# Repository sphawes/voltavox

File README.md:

# Voltavox
Voltavox is a PCB-based phonograph "badge"!

Made primarially from PCBs, you can take a tiny PCB record, place it on the platter, place the needle on the record, and a song begins to play! Put a different record on, and as expected, you'll get a different song.

Voltavox is based heavily on the [Adafruit Audio FX Sound Board](https://www.adafruit.com/product/2217). Using [arturo182](https://github.com/arturo182)'s [FlexyPins](https://lectronz.com/products/flexypin-pack-of-100) and some castellated edges on the record PCBs, each record selectively pulls a different control pin on the Audio FX board to ground, choosing a different track. Dropping the needle onto the record completes the circuit and starts playing the audio. 
The horn is also comprised of PCBs soldered edge-to-edge, with a small speaker inside.

## BOM
### Off The Shelf
| Item | Quantity |
| ---- | -------- |
| [Adafruit Audio FX Sound Board + 2x2W Amp - 16MB](https://www.adafruit.com/product/2217) | 1 |
| [8 Ohm Speaker](https://www.adafruit.com/product/1890) | 1 |
| [1200mAh LiPo Battery](https://www.adafruit.com/product/258) | 1 |
| [Micro-Lipo Charger](https://www.adafruit.com/product/1904) | 1 |
| [FlexyPins](https://lectronz.com/products/flexypin-pack-of-100) | 10 |
| [SPST Slide Switch](https://www.adafruit.com/product/805) | 1 |
| [Silicone Wire - 30AWG](https://www.adafruit.com/product/3169) | 1 |
| [P75-LM3 Spring Pin](https://www.adafruit.com/product/394) | 1 |
| [1x14 2.54mm SMT Header](https://www.digikey.com/en/products/detail/w%C3%BCrth-elektronik/61001418221/4846817) | 2 |
| [1x4 2.54mm SMT Header](https://www.digikey.com/en/products/detail/metz-connect-usa-inc/PM20204VBNN/12342877) | 1 |
| [Adhesive-Backed Green Felt](https://amzn.to/3xrK0NY) | 1 |
| [Dark Wood PLA Filament](https://amzn.to/3QOZQca) | 1 |
| [Record Label Stickers](https://www.amazon.com/dp/B06VX94JD8)| 1 |

### PCBs
| Item | Quantity | Order Instructions | Note |
| ---- | -------- | ------------------ | ---- |
| Record | 1+ | 1.6mm PCB, 1oz copper. Gloss Black Soldermask, Lead-Free HASL finish. | Has castellated pads to interface with the FlexyPins. Be sure to include a note to your board shop. | 
| Platter | 1 | 1.6mm PCB, 1oz copper. Matte Black Soldermask, Lead-Free HASL finish. | - |
| Needle | 1 | 1.6mm PCB, 1oz copper. Gloss Black Soldermask, Lead-Free HASL finish. | - |
| Horn Tier 1 | 8 | 1.6mm PCB, 1oz copper. Matte Black Soldermask, ENIG gold immersion finish. | Has castellated edges that are used for structural soldering. Be sure to include a note to your board shop.|
| Horn Tier 2 | 8 | 1.6mm PCB, 1oz copper. Matte Black Soldermask, ENIG gold immersion finish. | Has castellated edges that are used for structural soldering. Be sure to include a note to your board shop.|

### 3D Prints
| Item | Quantity | Material | Note |
| ---- | -------- | -------- | ---- |
| base | 1 | Wood PLA | Print with supports at 0.2mm layer height, 15% infill or more |
| horn-base-adapter | 1 | Silver PLA | Print with supports at 0.2mm layer height, 20% infill or more |
| drawer | 1 | Wood PLA | Print without supports at 0.2mm layer height, 15% infill or more |
| needle-mount | 1 | Silver PETG | Print without supports at 0.2mm layer height, 20% infill or more |
| pin | 1 | Silver PLA | Print without supports at 0.2mm layer height, 15% infill or more |

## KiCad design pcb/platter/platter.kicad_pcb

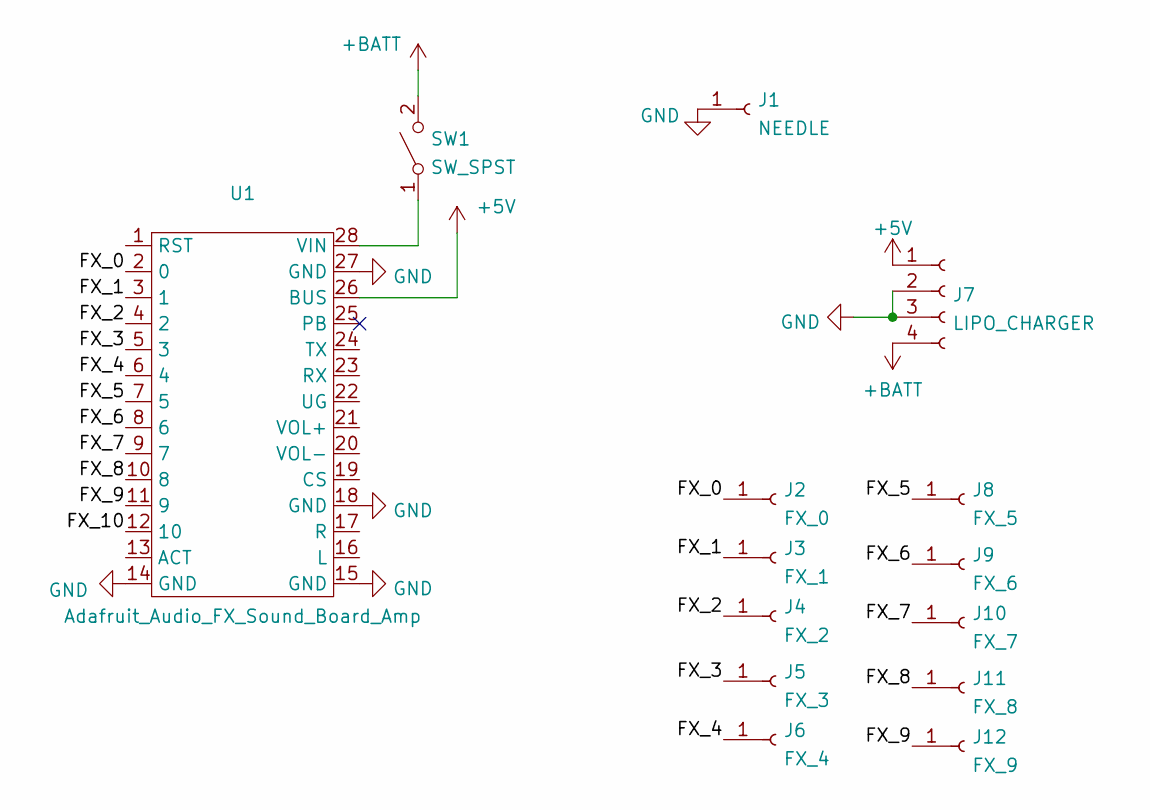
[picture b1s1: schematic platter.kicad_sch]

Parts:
J1: NEEDLE; TestPoint_Pad_D2.0mm
J2: FX_0; FlexyPin_1x01_P2.54mm
J3: FX_1; FlexyPin_1x01_P2.54mm
J4: FX_2; FlexyPin_1x01_P2.54mm
J5: FX_3; FlexyPin_1x01_P2.54mm
J6: FX_4; FlexyPin_1x01_P2.54mm
J7: LIPO_CHARGER; PinHeader_1x04_P2.54mm_Vertical_SMD_Pin1Left
J8: FX_5; FlexyPin_1x01_P2.54mm
J9: FX_6; FlexyPin_1x01_P2.54mm
J10: FX_7; FlexyPin_1x01_P2.54mm
J11: FX_8; FlexyPin_1x01_P2.54mm
J12: FX_9; FlexyPin_1x01_P2.54mm
SW1: SW_SPST; SolderJumper-2_P1.3mm_Open_Pad1.0x1.5mm
U1: Adafruit_Audio_FX_Sound_Board_Amp; Adafruit_Audio_FX_Board

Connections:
+5V: J7.1, U1.26 (BUS)
+BATT: J7.4, SW1.2 (B)
/FX_0: J2.1, U1.2 (0)
/FX_1: J3.1, U1.3 (1)
/FX_2: J4.1, U1.4 (2)
/FX_3: J5.1, U1.5 (3)
/FX_4: J6.1, U1.6 (4)
/FX_5: J8.1, U1.7 (5)
/FX_6: J9.1, U1.8 (6)
/FX_7: J10.1, U1.9 (7)
/FX_8: J11.1, U1.10 (8)
/FX_9: J12.1, U1.11 (9)
/FX_10: U1.12 (10)
GND: J1.1, J7.2, J7.3, U1.14 (GND), U1.15 (GND), U1.18 (GND), U1.27 (GND)
unnamed: SW1.1 (A), U1.28 (VIN)

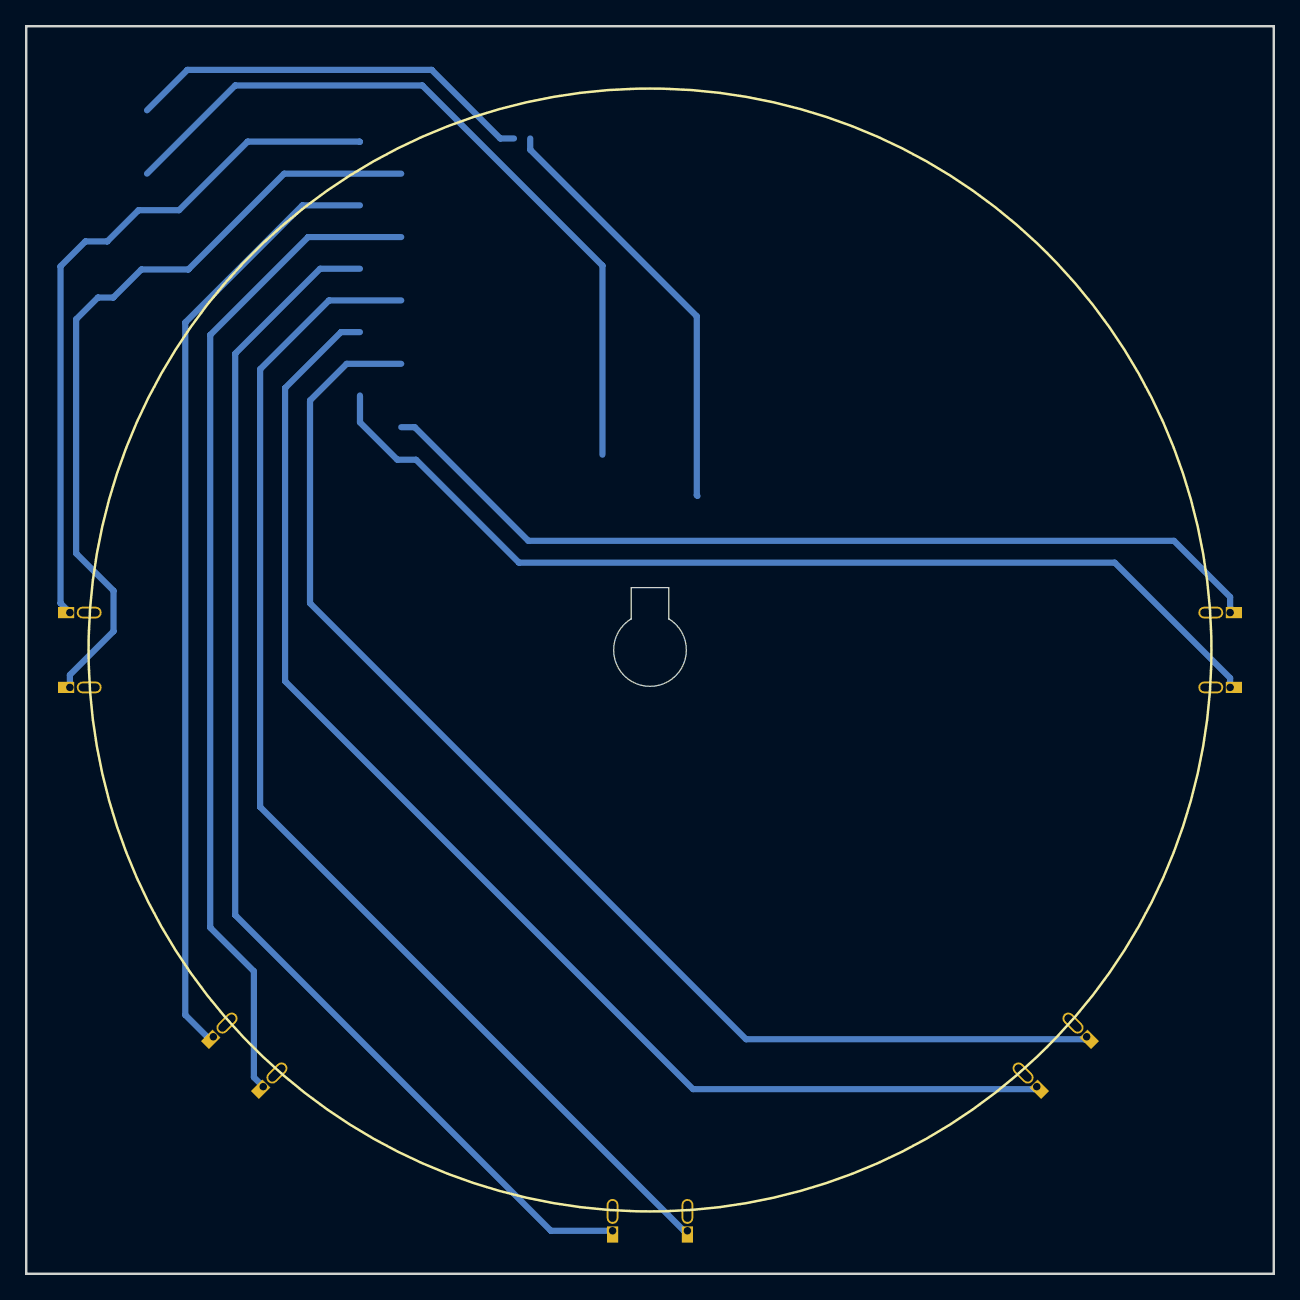
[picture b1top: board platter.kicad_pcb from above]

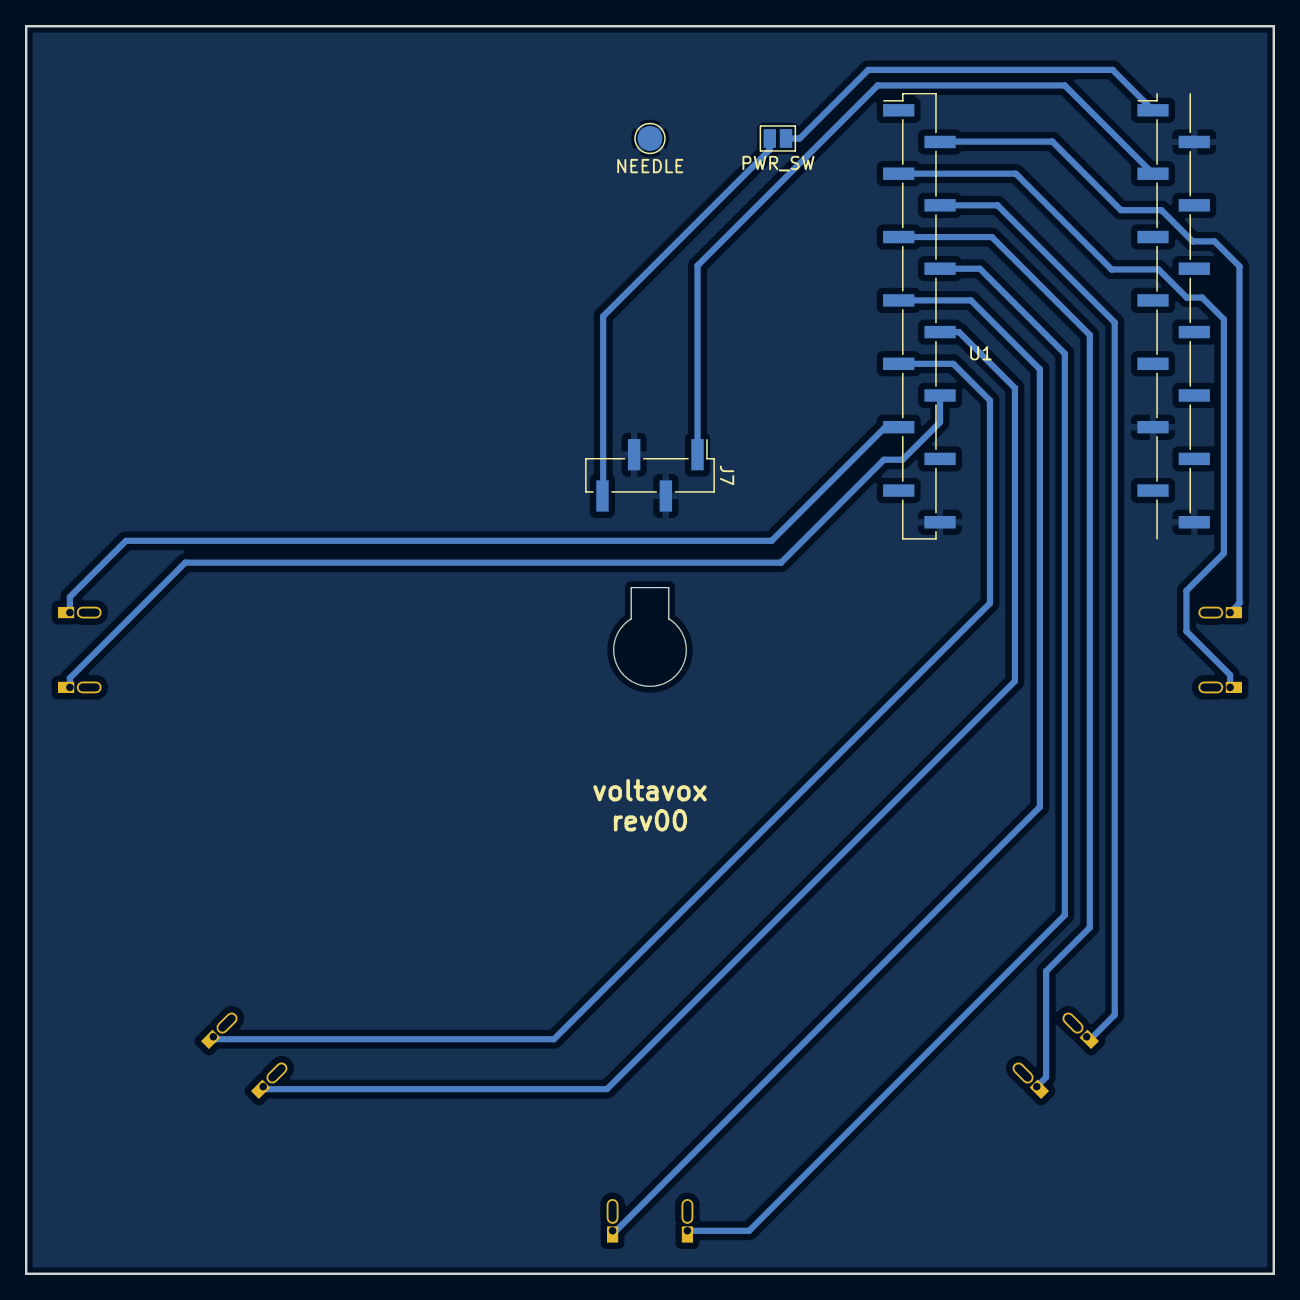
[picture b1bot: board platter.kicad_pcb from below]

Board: 2 copper layers, 100.0 x 100.0 mm, 14 parts (4 on the bottom side), 14 nets.

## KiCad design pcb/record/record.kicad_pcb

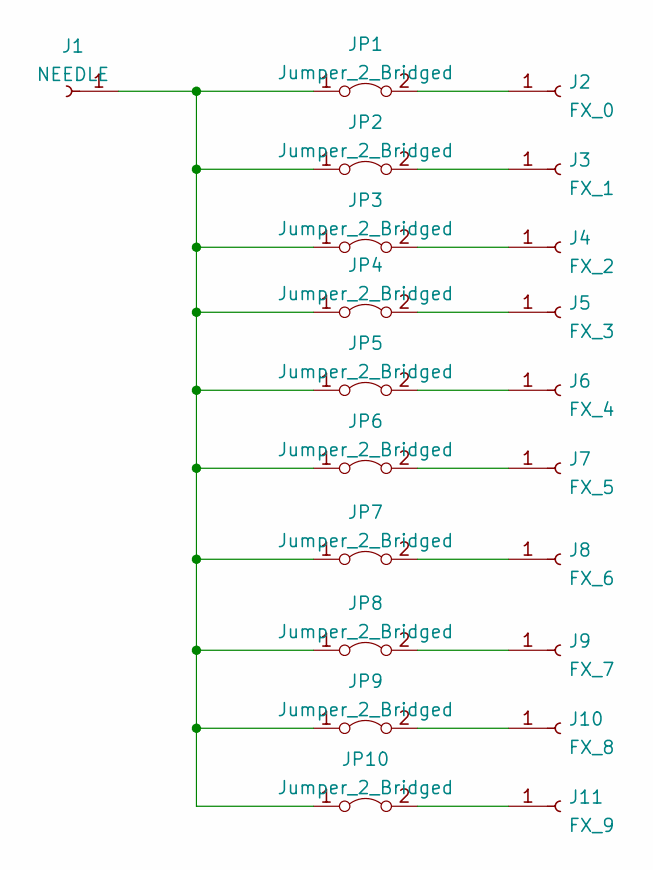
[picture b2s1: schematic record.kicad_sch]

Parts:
J1: NEEDLE; TestPoint_Pad_D4.0mm
J2: FX_0; TestPoint_Loop_D2.50mm_Drill1.0mm_LowProfile
J3: FX_1; TestPoint_Loop_D2.50mm_Drill1.0mm_LowProfile
J4: FX_2; TestPoint_Loop_D2.50mm_Drill1.0mm_LowProfile
J5: FX_3; TestPoint_Loop_D2.50mm_Drill1.0mm_LowProfile
J6: FX_4; TestPoint_Loop_D2.50mm_Drill1.0mm_LowProfile
J7: FX_5; TestPoint_Loop_D2.50mm_Drill1.0mm_LowProfile
J8: FX_6; TestPoint_Loop_D2.50mm_Drill1.0mm_LowProfile
J9: FX_7; TestPoint_Loop_D2.50mm_Drill1.0mm_LowProfile
J10: FX_8; TestPoint_Loop_D2.50mm_Drill1.0mm_LowProfile
J11: FX_9; TestPoint_Loop_D2.50mm_Drill1.0mm_LowProfile
JP1, JP2, JP3, JP4, JP5, JP6, JP7, JP8, JP9, JP10: Jumper_2_Bridged; SolderJumper-2_P1.3mm_Bridged_RoundedPad1.0x1.5mm

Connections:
unnamed: J1.1, JP1.1 (A), JP2.1 (A), JP3.1 (A), JP4.1 (A), JP5.1 (A), JP6.1 (A), JP7.1 (A), JP8.1 (A), JP9.1 (A), JP10.1 (A)
unnamed: J2.1, JP1.2 (B)
unnamed: J3.1, JP2.2 (B)
unnamed: J4.1, JP3.2 (B)
unnamed: J5.1, JP4.2 (B)
unnamed: J6.1, JP5.2 (B)
unnamed: J7.1, JP6.2 (B)
unnamed: J8.1, JP7.2 (B)
unnamed: J9.1, JP8.2 (B)
unnamed: J10.1, JP9.2 (B)
unnamed: J11.1, JP10.2 (B)

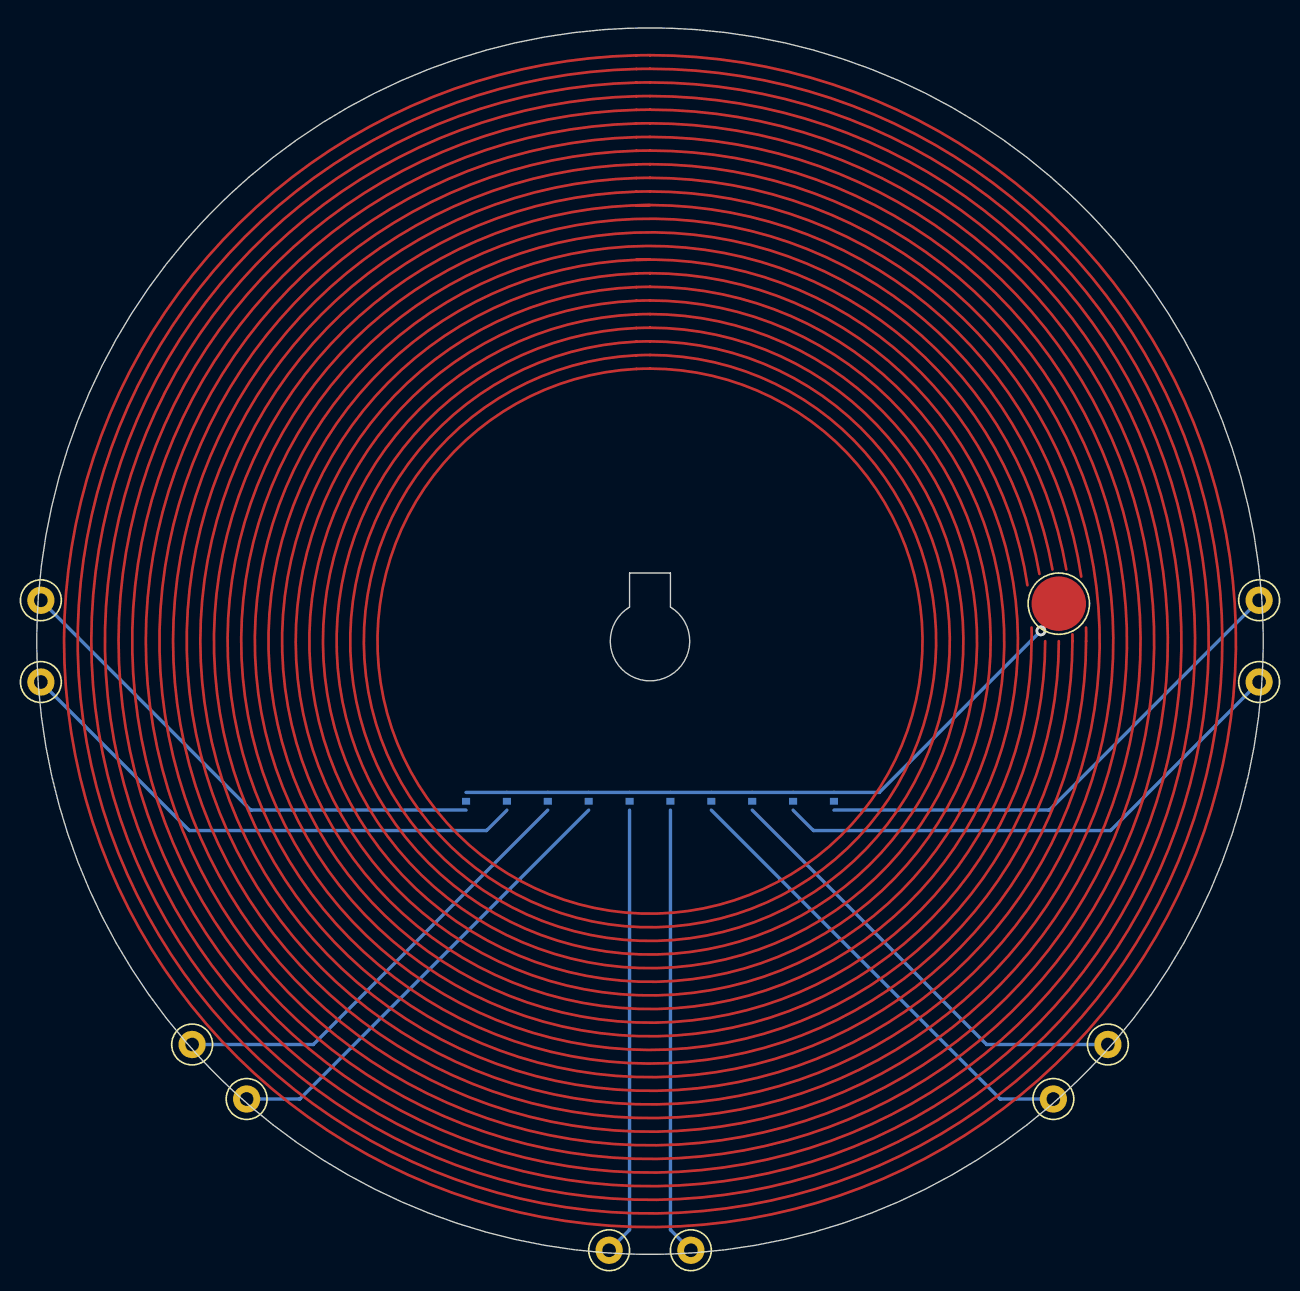
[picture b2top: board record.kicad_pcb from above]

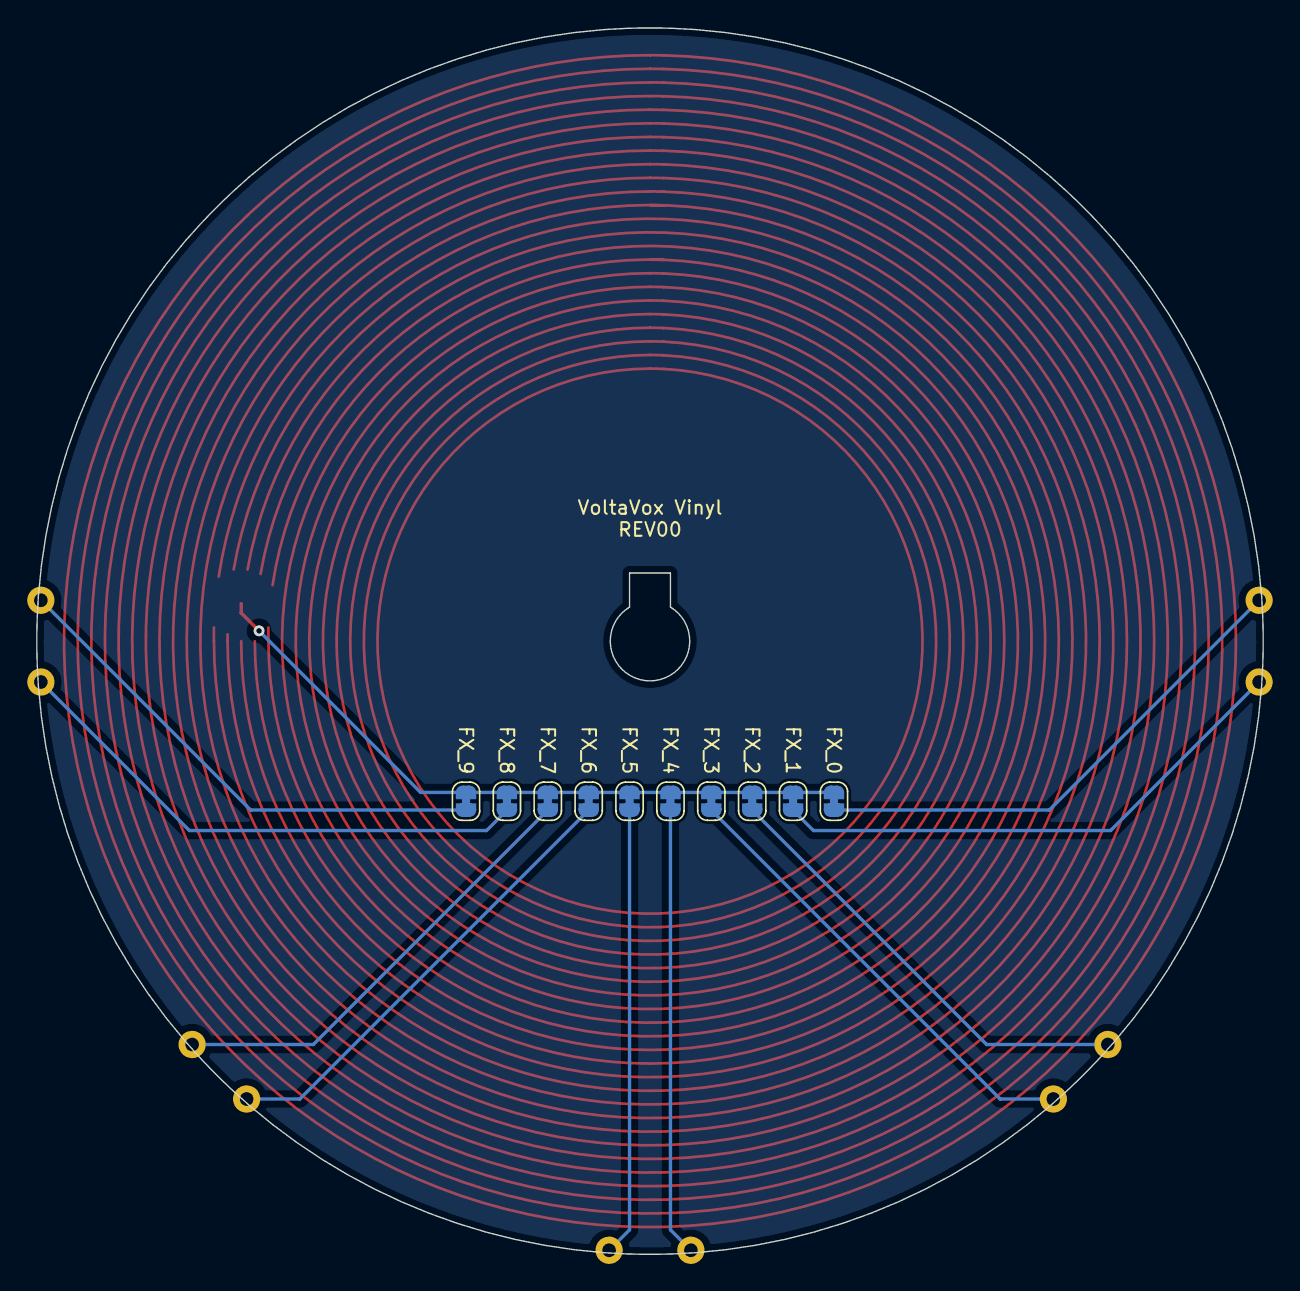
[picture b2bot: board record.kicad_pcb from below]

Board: 2 copper layers, 90.0 x 90.0 mm, 21 parts (10 on the bottom side), 11 nets.

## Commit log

2022-09-14 adds dsstore to gitignore
2022-09-14 adds bom to readme, adds platter and record pcbs
2022-09-15 adds horn-base-adapter files
    connects phonograph horn PCB panels to wire channel.
2022-09-15 fixes some readme errors
2022-09-15 readme tweaks
2022-09-15 adds voltavox box graphic
    a new folder with the .ai and .svg of a vector graphic for the box
2022-09-15 updates internal dimensions of horn-base-adapter
    test print didn't fit. this is an alteration of the interior diameter of the wire channel.
2022-09-15 adds pcb outlines for horn component
2022-09-15 moves needle pcb into repository
    this will need rework, but belongs in this repo for now.
2022-09-17 adds dxf of logo
2022-09-17 changes volta needle to spec
2022-09-17 updates length of needle pcb
2022-09-17 updates length of needle pcb
    again
2022-09-18 tweaks aesthetic things about the horn pcbs
    send Rev0 to JLC for manufacturing
2022-09-18 fixes folder pathways
2022-09-19 adds zipped folders for pcb production
2022-10-10 adjusts adapter and adds jigv1
2022-10-11 adds step file of horn
2022-11-03 adds record stickers to bom, changes horn base adapter to silver pla, adds pic
2022-11-03 adds stephens audio
2022-11-03 adds my music choices
2022-11-03 adds marvelous party track
    i couldn't've liked it more!
2022-11-03 adds blood
    bwahaha
2022-11-03 Fixing track 00
2022-11-03 cleans up cad files, updates readme to include pin
2022-11-03 suggesting supports for base print
